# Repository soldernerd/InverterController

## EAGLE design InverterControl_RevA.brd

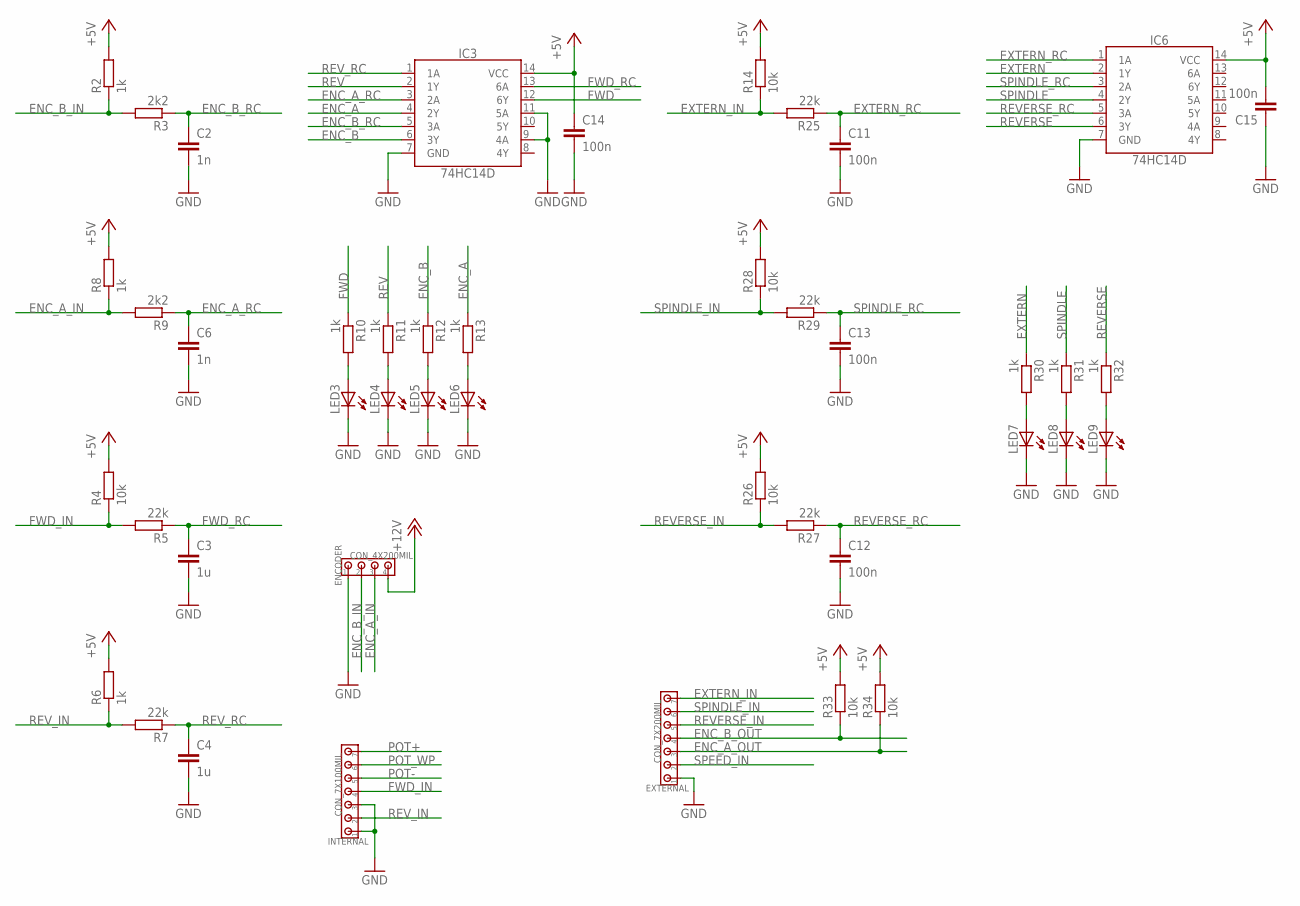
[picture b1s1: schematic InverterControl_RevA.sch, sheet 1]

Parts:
C2, C6: 1n; C0805
C3, C4: 1u; C0805
C11, C12, C13, C14, C15: 100n; C0805
ENCODER: CON_4X200MIL; 200MIL_4X
EXTERNAL: CON_7X200MIL; 200MIL_7X
IC3, IC6: 74HC14D; SO14
INTERNAL: CON_7X100MIL; 100MIL_7X
LED3, LED4, LED5, LED6, LED7, LED8, LED9: LED0805
R2, R6, R8, R10, R11, R12, R13, R30, R31, R32: 1k; R0805
R3, R9: 2k2; R0805
R4, R14, R26, R28, R33, R34: 10k; R0805
R5, R7, R25, R27, R29: 22k; R0805

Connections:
+5V: C14.1, C15.2, IC3.14 (VCC), IC6.14 (VCC), R2.2, R4.2, R6.2, R8.2, R14.2, R26.2, R28.2, R33.2, R34.2; also elsewhere on the board
+12V: ENCODER.4; also elsewhere on the board
ENC_A: IC3.4 (2Y), R13.1; also elsewhere on the board
ENC_A_IN: ENCODER.3, R8.1, R9.2
ENC_A_OUT: EXTERNAL.3, R34.1; also elsewhere on the board
ENC_A_RC: C6.1, IC3.3 (2A), R9.1
ENC_B: IC3.6 (3Y), R12.1; also elsewhere on the board
ENC_B_IN: ENCODER.2, R2.1, R3.2
ENC_B_OUT: EXTERNAL.4, R33.1; also elsewhere on the board
ENC_B_RC: C2.1, IC3.5 (3A), R3.1
EXTERN: IC6.2 (1Y), R30.1; also elsewhere on the board
EXTERN_IN: EXTERNAL.7, R14.1, R25.2
EXTERN_RC: C11.1, IC6.1 (1A), R25.1
FWD: IC3.12 (6Y), R10.1; also elsewhere on the board
FWD_IN: INTERNAL.4, R4.1, R5.2
FWD_RC: C3.1, IC3.13 (6A), R5.1
GND: C2.2, C3.2, C4.2, C6.2, C11.2, C12.2, C13.2, C14.2, C15.1, ENCODER.1, EXTERNAL.1, IC3.7 (GND), IC3.9 (4A), IC3.11 (5A), IC6.7 (GND), INTERNAL.1, INTERNAL.3, LED3.C, LED4.C, LED5.C, LED6.C, LED7.C, LED8.C, LED9.C; also elsewhere on the board
unnamed: LED3.A, R10.2
unnamed: LED4.A, R11.2
unnamed: LED5.A, R12.2
unnamed: LED7.A, R30.2
unnamed: LED6.A, R13.2
unnamed: LED8.A, R31.2
unnamed: LED9.A, R32.2
POT+: INTERNAL.7; also elsewhere on the board
POT-: INTERNAL.5; also elsewhere on the board
POT_WP: INTERNAL.6; also elsewhere on the board
REV: IC3.2 (1Y), R11.1; also elsewhere on the board
REVERSE: IC6.6 (3Y), R32.1; also elsewhere on the board
REVERSE_IN: EXTERNAL.5, R26.1, R27.2
REVERSE_RC: C12.1, IC6.5 (3A), R27.1
REV_IN: INTERNAL.2, R6.1, R7.2
REV_RC: C4.1, IC3.1 (1A), R7.1
SPEED_IN: EXTERNAL.2; also elsewhere on the board
SPINDLE: IC6.4 (2Y), R31.1; also elsewhere on the board
SPINDLE_IN: EXTERNAL.6, R28.1, R29.2
SPINDLE_RC: C13.1, IC6.3 (2A), R29.1

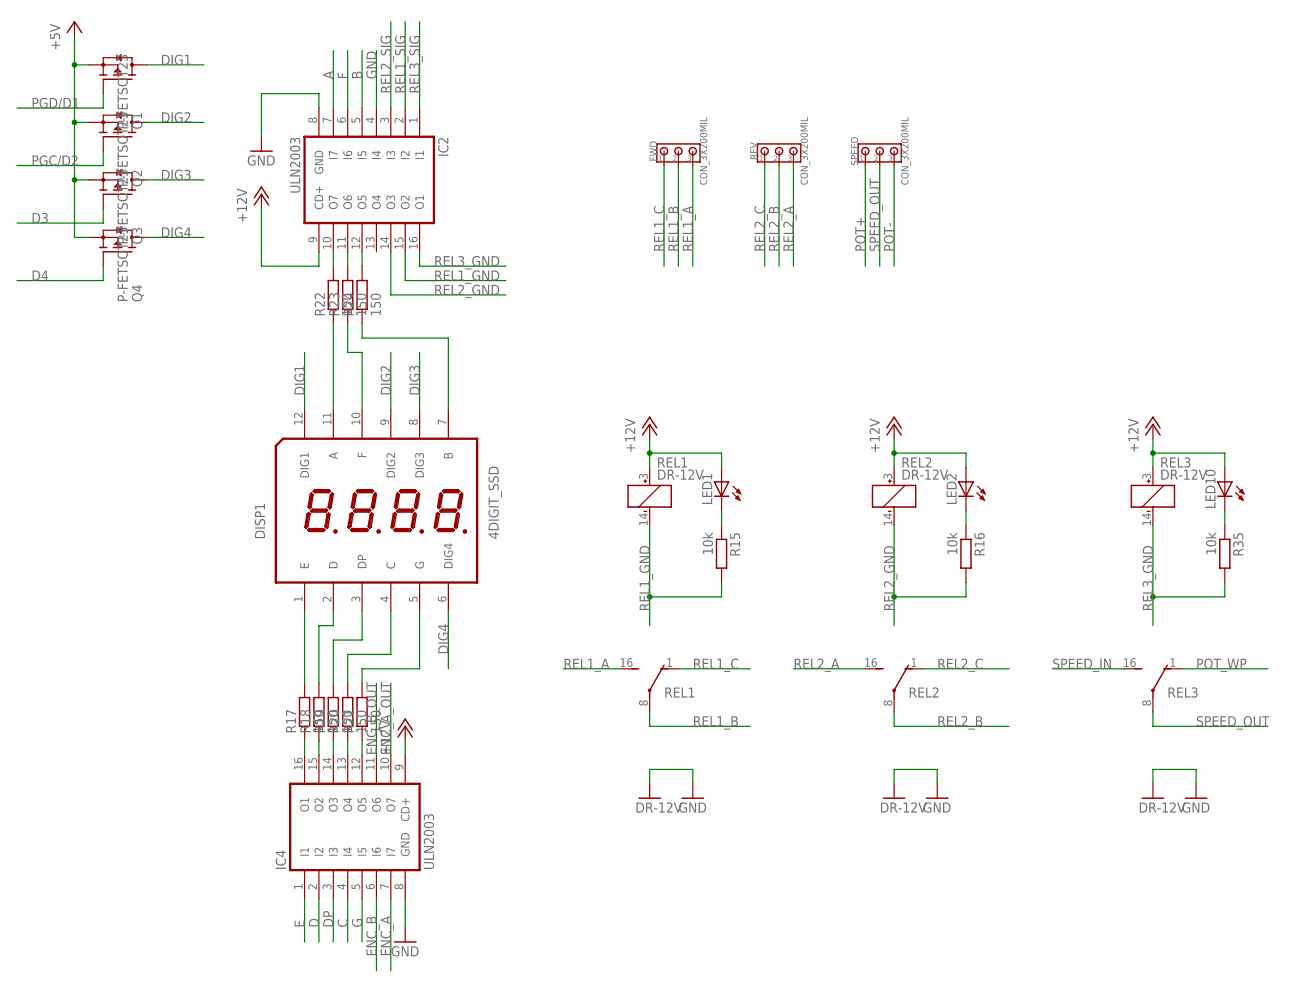
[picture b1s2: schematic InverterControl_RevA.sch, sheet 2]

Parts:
DISP1: 4DIGIT_SSD
FWD: CON_3X200MIL; 200MIL_3X
IC2, IC4: ULN2003; SO16
LED1, LED2, LED10: LED0805
Q1, Q2, Q3, Q4: P-FETSOT23; SOT23
R15, R16, R35: 10k; R0805
R17, R18, R19, R20, R21, R22, R23, R24: 150; R0805
REL1, REL2, REL3: DR-12V
REV: CON_3X200MIL; 200MIL_3X
SPEED: CON_3X200MIL; 200MIL_3X

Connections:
+5V: Q1.2 (S), Q2.2 (S), Q3.2 (S), Q4.2 (S); also elsewhere on the board
+12V: IC2.9 (CD+), IC4.9 (CD+), LED1.A, LED2.A, LED10.A, REL1.3 (+), REL2.3 (+), REL3.3 (+); also elsewhere on the board
A: IC2.7 (I7); also elsewhere on the board
B: IC2.5 (I5); also elsewhere on the board
C: IC4.4 (I4); also elsewhere on the board
D: IC4.2 (I2); also elsewhere on the board
D3: Q3.1 (G); also elsewhere on the board
D4: Q4.1 (G); also elsewhere on the board
DIG1: DISP1.12 (DIG1), Q1.3 (D)
DIG2: DISP1.9 (DIG2), Q2.3 (D)
DIG3: DISP1.8 (DIG3), Q3.3 (D)
DIG4: DISP1.6 (DIG4), Q4.3 (D)
DP: IC4.3 (I3); also elsewhere on the board
E: IC4.1 (I1); also elsewhere on the board
ENC_A: IC4.7 (I7); also elsewhere on the board
ENC_A_OUT: IC4.10 (O7); also elsewhere on the board
ENC_B: IC4.6 (I6); also elsewhere on the board
ENC_B_OUT: IC4.11 (O6); also elsewhere on the board
F: IC2.6 (I6); also elsewhere on the board
G: IC4.5 (I5); also elsewhere on the board
GND: IC2.4 (I4), IC2.8 (GND), IC4.8 (GND), REL1.9 (GND), REL2.9 (GND), REL3.9 (GND); also elsewhere on the board
unnamed: DISP1.1 (E), R17.2
unnamed: DISP1.2 (D), R18.2
unnamed: LED1.C, R15.1
unnamed: LED2.C, R16.1
unnamed: DISP1.3 (DP), R19.2
unnamed: DISP1.4 (C), R20.2
unnamed: DISP1.5 (G), R21.2
unnamed: DISP1.11 (A), R22.1
unnamed: DISP1.10 (F), R23.1
unnamed: DISP1.7 (B), R24.1
unnamed: IC4.16 (O1), R17.1
unnamed: IC4.15 (O2), R18.1
unnamed: IC4.14 (O3), R19.1
unnamed: IC4.13 (O4), R20.1
unnamed: IC4.12 (O5), R21.1
unnamed: IC2.10 (O7), R22.2
unnamed: IC2.11 (O6), R23.2
unnamed: IC2.12 (O5), R24.2
unnamed: LED10.C, R35.1
PGC/D2: Q2.1 (G); also elsewhere on the board
PGD/D1: Q1.1 (G); also elsewhere on the board
POT+: SPEED.1; also elsewhere on the board
POT-: SPEED.3; also elsewhere on the board
POT_WP: REL3.1 (NC); also elsewhere on the board
REL1_A: FWD.3, REL1.16 (NO)
REL1_B: FWD.2, REL1.8 (COM)
REL1_C: FWD.1, REL1.1 (NC)
REL1_GND: IC2.15 (O2), R15.2, REL1.14 (-)
REL1_SIG: IC2.2 (I2); also elsewhere on the board
REL2_A: REL2.16 (NO), REV.3
REL2_B: REL2.8 (COM), REV.2
REL2_C: REL2.1 (NC), REV.1
REL2_GND: IC2.14 (O3), R16.2, REL2.14 (-)
REL2_SIG: IC2.3 (I3); also elsewhere on the board
REL3_GND: IC2.16 (O1), R35.2, REL3.14 (-)
REL3_SIG: IC2.1 (I1); also elsewhere on the board
SPEED_IN: REL3.16 (NO); also elsewhere on the board
SPEED_OUT: REL3.8 (COM), SPEED.2

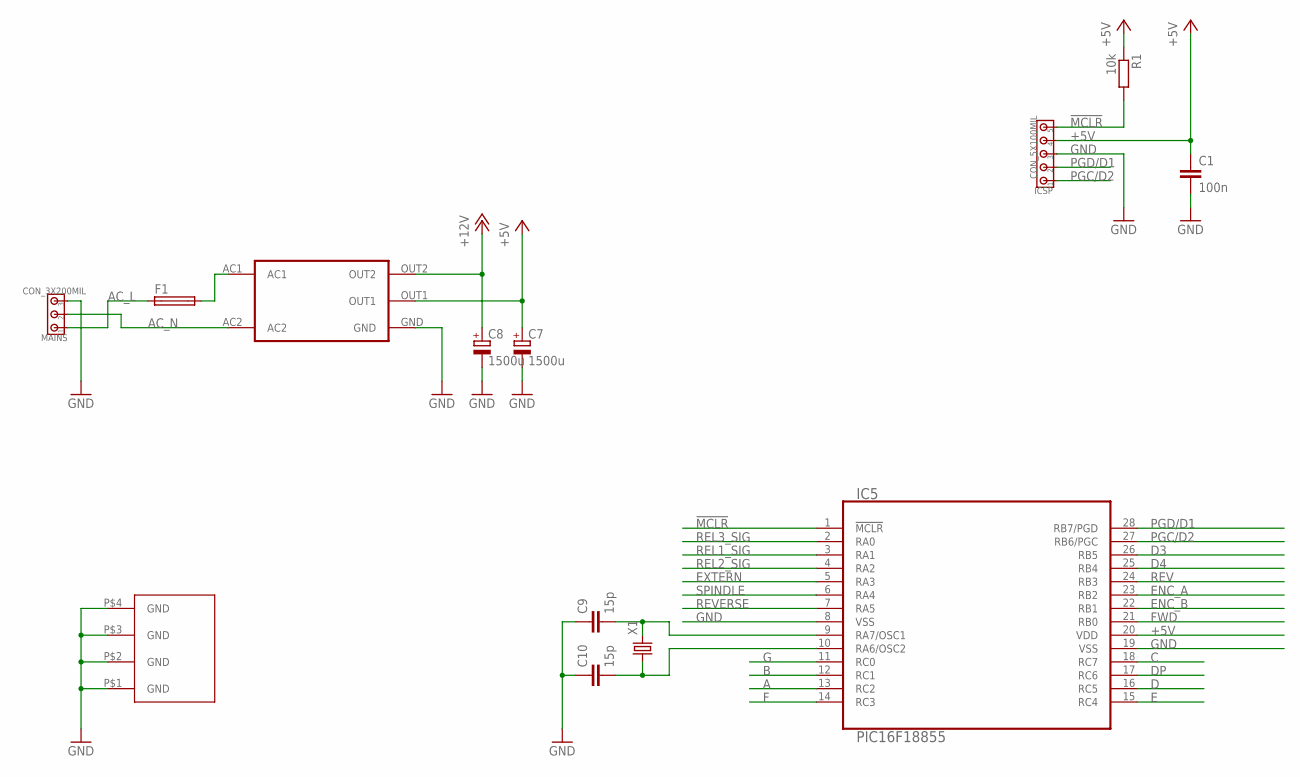
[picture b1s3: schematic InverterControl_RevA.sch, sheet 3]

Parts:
ACDC1: MYRRA47246; MYRRA47000
C1: 100n; C0805
C7, C8: 1500u; 10MM
C9, C10: 15p; C0805
F1: SH22,5
IC5: PIC16F18855; SO28W
ICSP: CON_5X100MIL; 100MIL_5X
MAINS: CON_3X200MIL; 200MIL_3X
R1: 10k; R0805
U$1: PCB_SPEED_METER; PBC_SPEED_METER
X1: CRYSTAL5X3.2MM; 5X3.2MM

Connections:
!MCLR!: IC5.1 (!MCLR!), ICSP.5, R1.2
+5V: ACDC1.OUT1, C1.1, C7.+, IC5.20 (VDD), ICSP.4, R1.1; also elsewhere on the board
+12V: ACDC1.OUT2, C8.+; also elsewhere on the board
A: IC5.13 (RC2); also elsewhere on the board
AC_L: F1.1, MAINS.1
AC_N: ACDC1.AC2, MAINS.2
B: IC5.12 (RC1); also elsewhere on the board
C: IC5.18 (RC7); also elsewhere on the board
D: IC5.16 (RC5); also elsewhere on the board
D3: IC5.26 (RB5); also elsewhere on the board
D4: IC5.25 (RB4); also elsewhere on the board
DP: IC5.17 (RC6); also elsewhere on the board
E: IC5.15 (RC4); also elsewhere on the board
ENC_A: IC5.23 (RB2); also elsewhere on the board
ENC_B: IC5.22 (RB1); also elsewhere on the board
EXTERN: IC5.5 (RA3); also elsewhere on the board
F: IC5.14 (RC3); also elsewhere on the board
FWD: IC5.21 (RB0); also elsewhere on the board
G: IC5.11 (RC0); also elsewhere on the board
GND: ACDC1.GND, C1.2, C7.-, C8.-, C9.1, C10.1, IC5.8 (VSS), IC5.19 (VSS), ICSP.3, MAINS.3, U$1.P$1, U$1.P$2, U$1.P$3, U$1.P$4; also elsewhere on the board
unnamed: ACDC1.AC1, F1.2
unnamed: C10.2, IC5.10 (RA6/OSC2), X1.1
unnamed: C9.2, IC5.9 (RA7/OSC1), X1.2
PGC/D2: IC5.27 (RB6/PGC), ICSP.1; also elsewhere on the board
PGD/D1: IC5.28 (RB7/PGD), ICSP.2; also elsewhere on the board
REL1_SIG: IC5.3 (RA1); also elsewhere on the board
REL2_SIG: IC5.4 (RA2); also elsewhere on the board
REL3_SIG: IC5.2 (RA0); also elsewhere on the board
REV: IC5.24 (RB3); also elsewhere on the board
REVERSE: IC5.7 (RA5); also elsewhere on the board
SPINDLE: IC5.6 (RA4); also elsewhere on the board

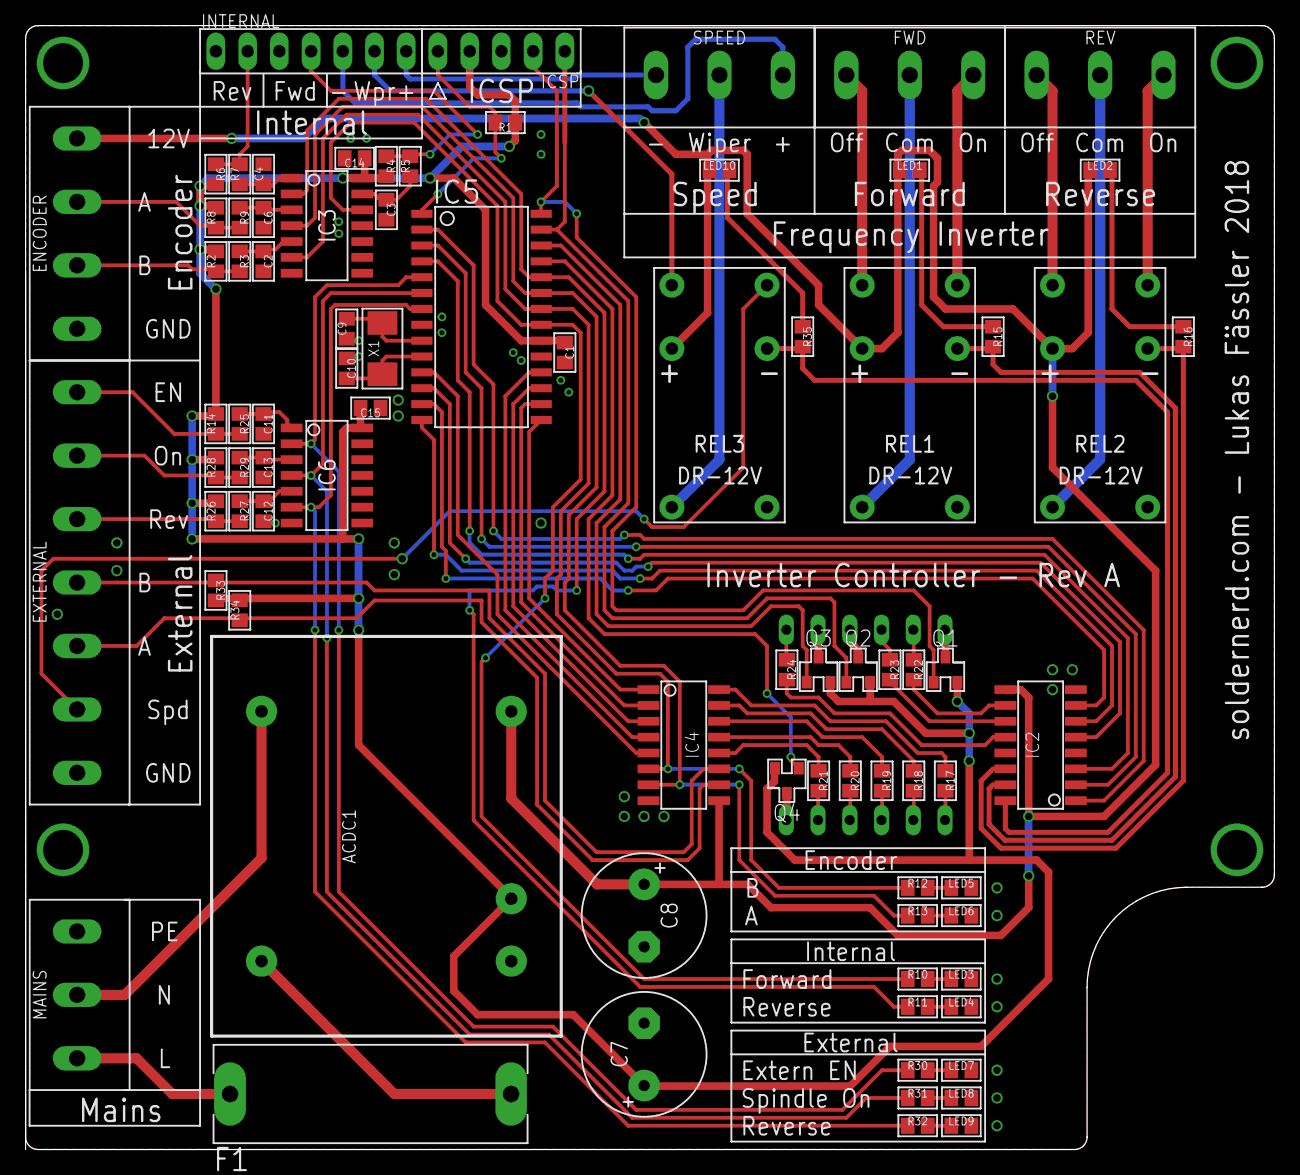
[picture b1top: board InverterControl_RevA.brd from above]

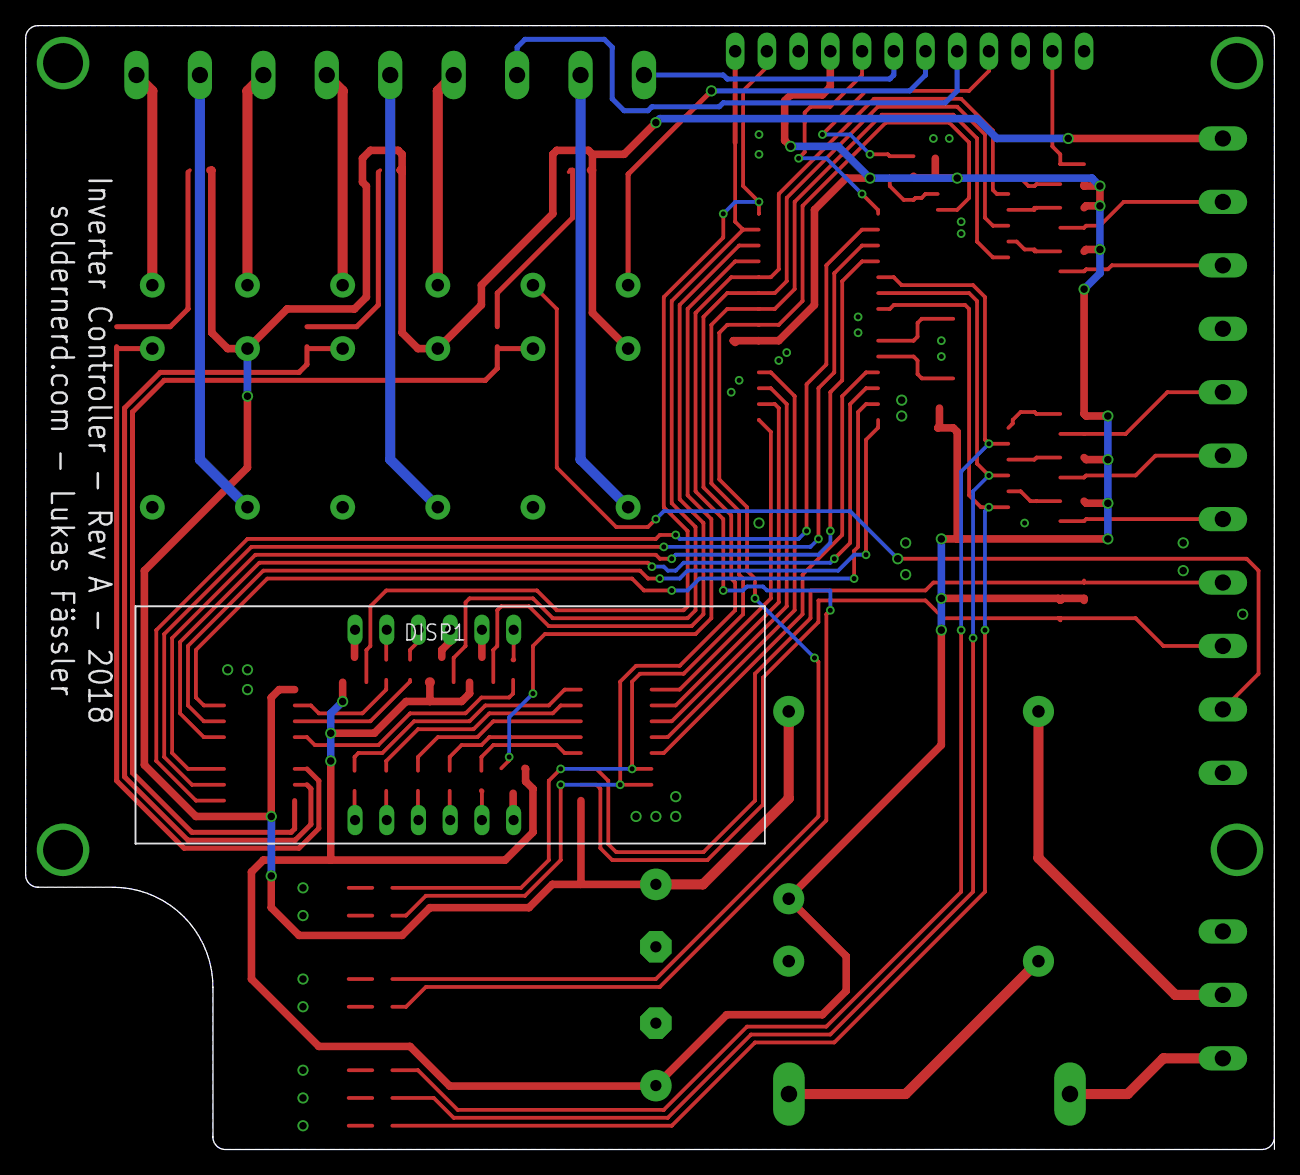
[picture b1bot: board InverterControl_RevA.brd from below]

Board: 2 copper layers, 100.0 x 90.0 mm, 84 parts (2 on the bottom side), 91 nets.

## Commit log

2018-06-25 Initial commit but already as ordered (Rev A)
